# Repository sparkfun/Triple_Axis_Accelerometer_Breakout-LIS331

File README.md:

SparkFun Triple Axis Accelerometer Breakout - LIS331
========================================

[*SparkFun Triple Axis Accelerometer Breakout - LIS331 (SEN-10345)*](https://www.sparkfun.com/products/10345)

 This is a breakout board for the ultra low-power LIS331HH three axis linear accelerometer. 
 The device has a digital I2C/SPI serial interface which makes it ideal for using in embedded applications. 
 All major pins are broken out to 0.1" spaced headers. It also includes two mounting holes as well.
 
Repository Contents
-------------------

* **/Firmware** - Example code 
* **/Hardware** - Eagle design files (.brd, .sch)
* **/Production** - Production panel files (.brd)

Documentation
--------------
* **[SparkFun Fritzing repo](https://github.com/sparkfun/Fritzing_Parts)** - Fritzing diagrams for SparkFun products.
* **[SparkFun 3D Model repo](https://github.com/sparkfun/3D_Models)** - 3D models of SparkFun products. 
* **[Project Tutorial](https://learn.sparkfun.com/tutorials/raspberry-pi-zero-helmet-impact-force-monitor)** - Project tutorial using the LIS331 on a Raspberry Pi. The code used in the project uses Python and linked in a [different GitHub repository](https://github.com/jenfoxbot/ImpactForceMonitor). 

License Information
-------------------
This product is _**open source**_! 

The **hardware** is released under [Creative Commons ShareAlike 4.0 International](https://creativecommons.org/licenses/by-sa/4.0/).

The **code** is beerware; if you see me (or any other SparkFun employee) at the local, and you've found our code helpful, please buy us a round!

Please use, reuse, and modify these files as you see fit. Please maintain attribution to SparkFun Electronics and release anything derivative under the same license.

Distributed as-is; no warranty is given.

- Your friends at SparkFun.

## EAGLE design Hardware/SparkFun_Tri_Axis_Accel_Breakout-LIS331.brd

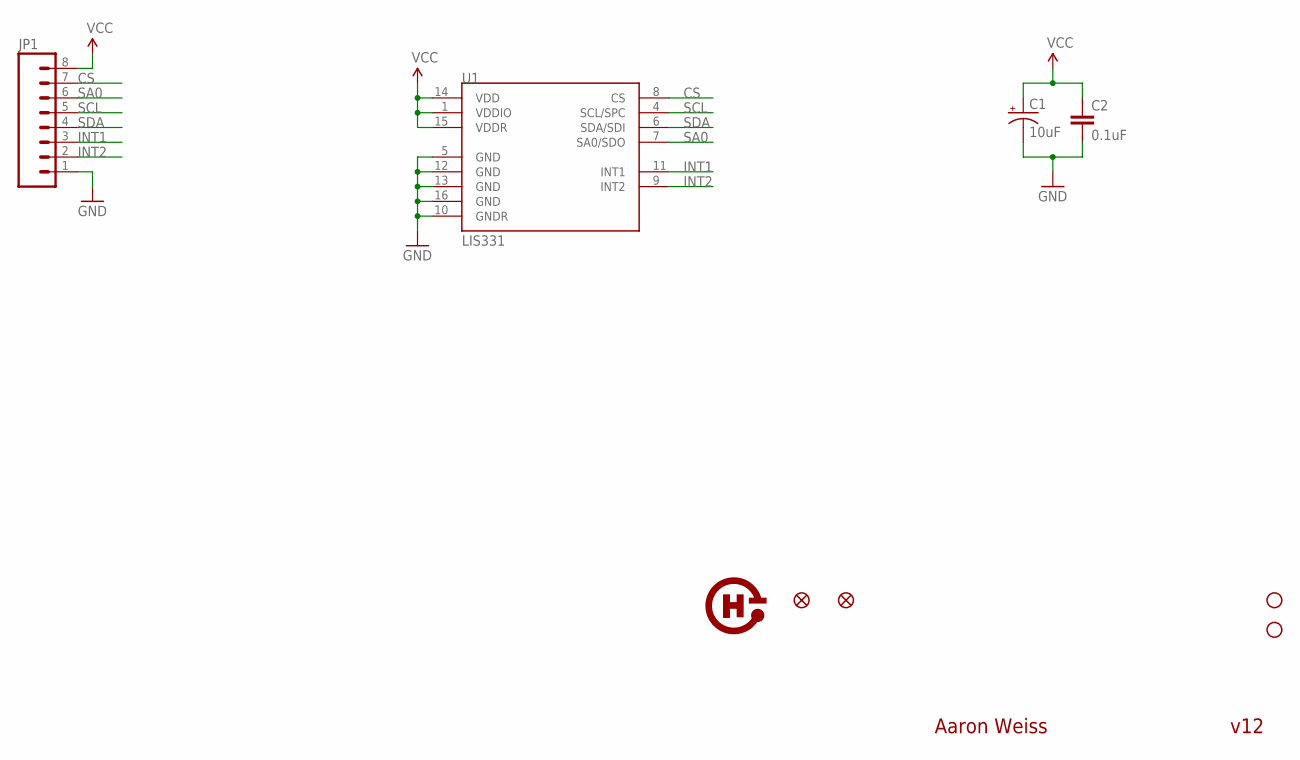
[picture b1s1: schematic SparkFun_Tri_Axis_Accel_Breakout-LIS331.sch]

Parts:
C1: 10uF; EIA3216
C2: 0.1uF; 0402-CAP
JP1: M08; 1X08
JP3, JP4: STAND-OFF
JP5, JP6: FIDUCIAL1X2; FIDUCIAL-1X2
U1: LIS331; LGA16-3MM
U$1: OSHW-LOGO-SMALL

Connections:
CS: JP1.7, U1.8 (CS)
GND: C1.C (-), C2.2, JP1.1, U1.5 (GND), U1.10 (GNDR), U1.12 (GND), U1.13 (GND), U1.16 (GND)
INT1: JP1.3, U1.11 (INT1)
INT2: JP1.2, U1.9 (INT2)
SA0: JP1.6, U1.7 (SA0/SDO)
SCL: JP1.5, U1.4 (SCL/SPC)
SDA: JP1.4, U1.6 (SDA/SDI)
VCC: C1.A (+), C2.1, JP1.8, U1.1 (VDDIO), U1.14 (VDD), U1.15 (VDDR)

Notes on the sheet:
v12
Aaron Weiss

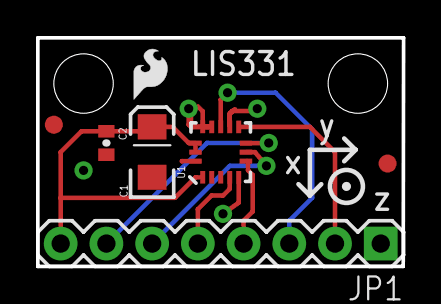
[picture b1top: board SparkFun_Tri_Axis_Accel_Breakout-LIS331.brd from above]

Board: 2 copper layers, 20.3 x 12.7 mm, 10 parts (1 on the bottom side), 8 nets.

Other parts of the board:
JP2: LOGO-SFESK; SFE-LOGO-FLAME

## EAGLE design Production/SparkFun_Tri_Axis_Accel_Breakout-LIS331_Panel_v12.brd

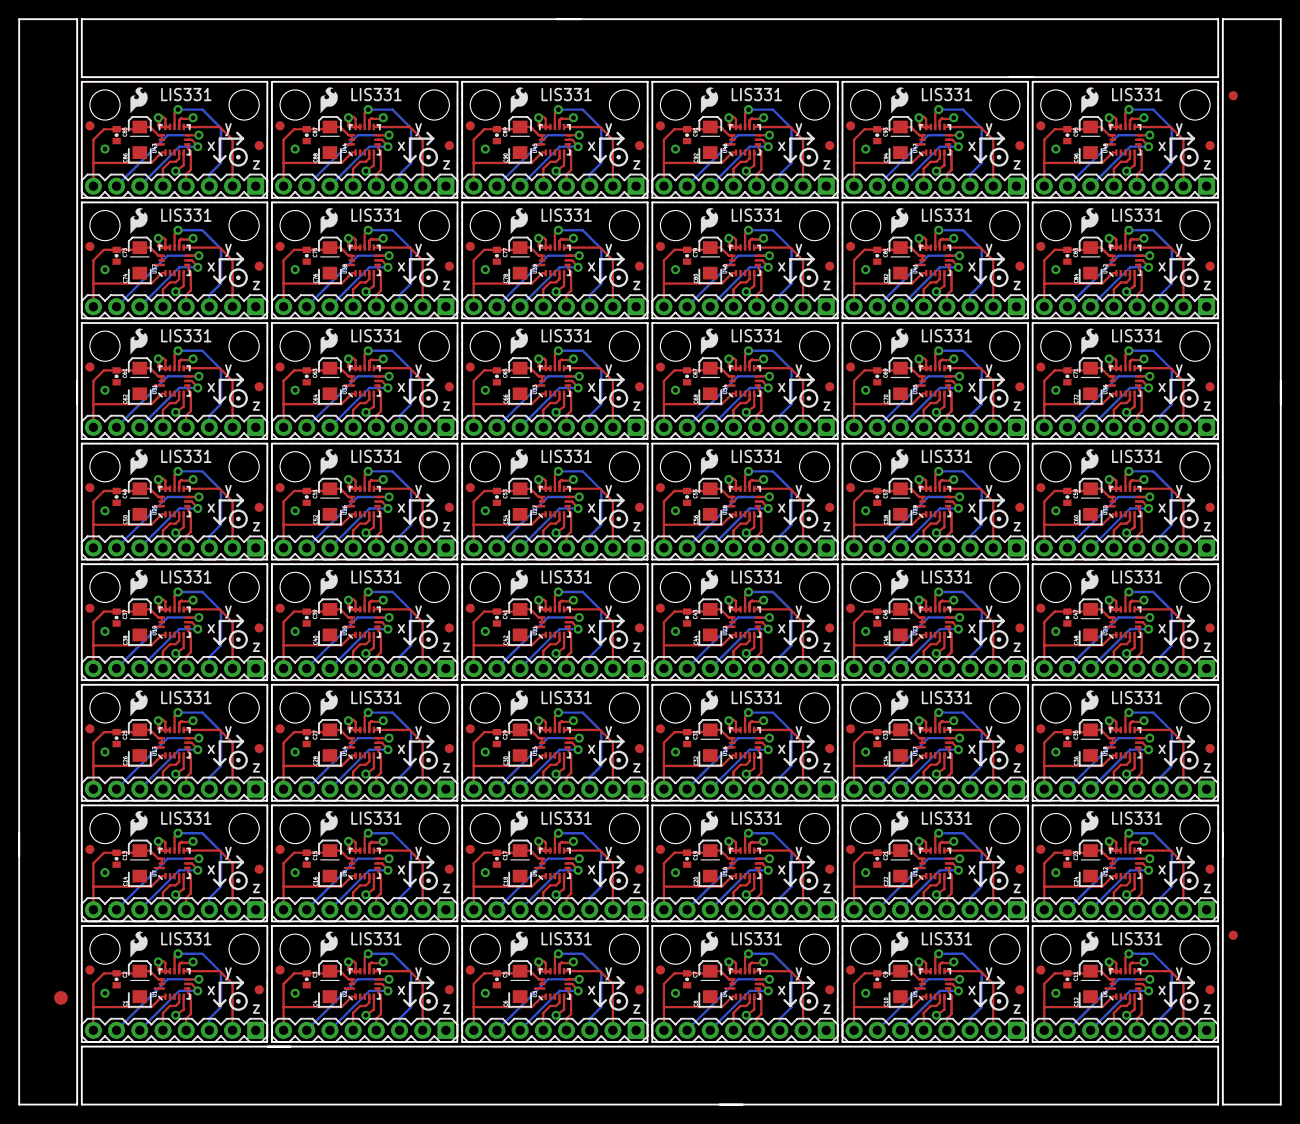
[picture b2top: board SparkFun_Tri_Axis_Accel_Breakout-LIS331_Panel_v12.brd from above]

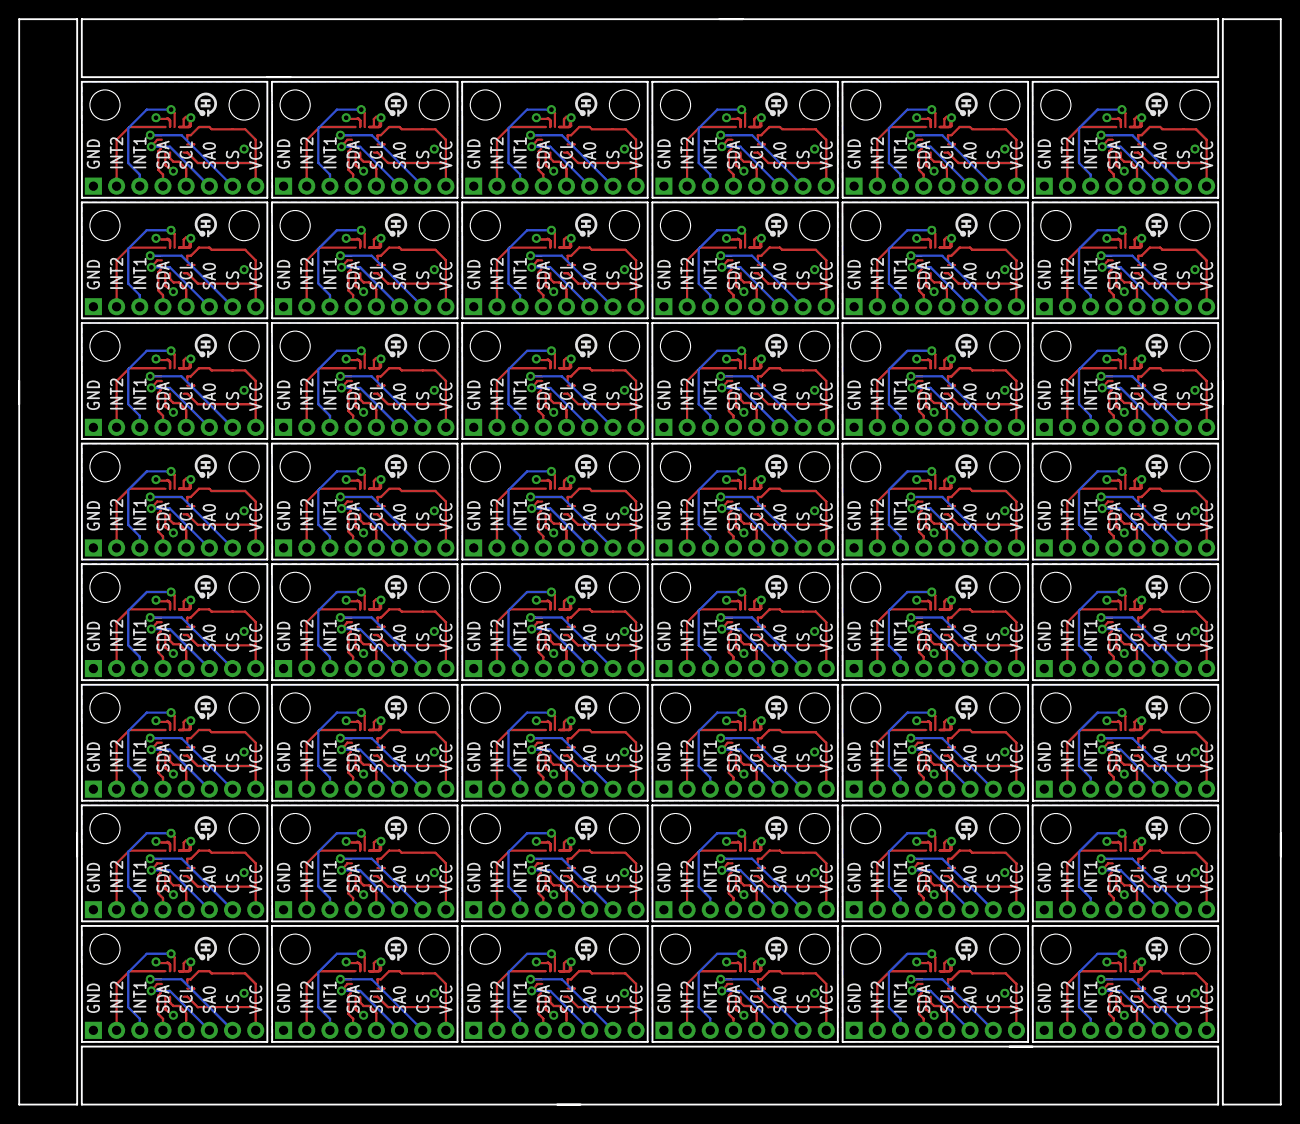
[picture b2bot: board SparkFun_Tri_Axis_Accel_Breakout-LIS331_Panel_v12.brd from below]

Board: 2 copper layers, 138.2 x 118.9 mm, 483 parts (48 on the bottom side), 384 nets.

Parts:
C1, C4, C6, C8, C10, C12, C14, C16, C18, C20, C22, C24, C26, C28, C30, C32, C34, C36, C38, C40, C42, C44, C46, C48, C50, C52, C54, C56, C58, C60, C62, C64, C66, C68, C70, C72, C74, C76, C78, C80, C82, C84, C86, C88, C90, C92, C94, C96: 10uF; EIA3216
C2, C3, C5, C7, C9, C11, C13, C15, C17, C19, C21, C23, C25, C27, C29, C31, C33, C35, C37, C39, C41, C43, C45, C47, C49, C51, C53, C55, C57, C59, C61, C63, C65, C67, C69, C71, C73, C75, C77, C79, C81, C83, C85, C87, C89, C91, C93, C95: 0.1uF; 0402-CAP
E$1: FIDUCIAL-1.5X3
E$5, E$6: FIDUCIAL-1X2
JP1, JP8, JP14, JP20, JP26, JP32, JP38, JP44, JP50, JP56, JP62, JP68, JP74, JP80, JP86, JP92, JP98, JP104, JP110, JP116, JP122, JP128, JP134, JP140, JP146, JP152, JP158, JP164, JP170, JP176, JP182, JP188, JP194, JP200, JP206, JP212, JP218, JP224, JP230, JP236, JP242, JP248, JP254, JP260, JP266, JP272, JP278, JP284: 1X08
JP2, JP7, JP13, JP19, JP25, JP31, JP37, JP43, JP49, JP55, JP61, JP67, JP73, JP79, JP85, JP91, JP97, JP103, JP109, JP115, JP121, JP127, JP133, JP139, JP145, JP151, JP157, JP163, JP169, JP175, JP181, JP187, JP193, JP199, JP205, JP211, JP217, JP223, JP229, JP235, JP241, JP247, JP253, JP259, JP265, JP271, JP277, JP283: LOGO-SFESK; SFE-LOGO-FLAME
JP3, JP4, JP9, JP10, JP15, JP16, JP21, JP22, JP27, JP28, JP33, JP34, JP39, JP40, JP45, JP46, JP51, JP52, JP57, JP58, JP63, JP64, JP69, JP70, JP75, JP76, JP81, JP82, JP87, JP88, JP93, JP94, JP99, JP100, JP105, JP106, JP111, JP112, JP117, JP118, JP123, JP124, JP129, JP130, JP135, JP136, JP141, JP142, JP147, JP148, JP153, JP154, JP159, JP160, JP165, JP166, JP171, JP172, JP177, JP178, JP183, JP184, JP189, JP190, JP195, JP196, JP201, JP202, JP207, JP208, JP213, JP214, JP219, JP220, JP225, JP226, JP231, JP232, JP237, JP238, JP243, JP244, JP249, JP250, JP255, JP256, JP261, JP262, JP267, JP268, JP273, JP274, JP279, JP280, JP285, JP286: STAND-OFF
JP5, JP6, JP11, JP12, JP17, JP18, JP23, JP24, JP29, JP30, JP35, JP36, JP41, JP42, JP47, JP48, JP53, JP54, JP59, JP60, JP65, JP66, JP71, JP72, JP77, JP78, JP83, JP84, JP89, JP90, JP95, JP96, JP101, JP102, JP107, JP108, JP113, JP114, JP119, JP120, JP125, JP126, JP131, JP132, JP137, JP138, JP143, JP144, JP149, JP150, JP155, JP156, JP161, JP162, JP167, JP168, JP173, JP174, JP179, JP180, JP185, JP186, JP191, JP192, JP197, JP198, JP203, JP204, JP209, JP210, JP215, JP216, JP221, JP222, JP227, JP228, JP233, JP234, JP239, JP240, JP245, JP246, JP251, JP252, JP257, JP258, JP263, JP264, JP269, JP270, JP275, JP276, JP281, JP282, JP287, JP288: FIDUCIAL1X2; FIDUCIAL-1X2
U1, U2, U3, U4, U5, U6, U7, U8, U9, U10, U11, U12, U13, U14, U15, U16, U17, U18, U19, U20, U21, U22, U23, U24, U25, U26, U27, U28, U29, U30, U31, U32, U33, U34, U35, U36, U37, U38, U39, U40, U41, U42, U43, U44, U45, U46, U47, U48: LIS331; LGA16-3MM
U$1, U$2, U$3, U$4, U$5, U$6, U$7, U$8, U$9, U$10, U$11, U$12, U$13, U$14, U$15, U$16, U$17, U$18, U$19, U$20, U$21, U$22, U$23, U$24, U$25, U$26, U$27, U$28, U$29, U$30, U$31, U$32, U$33, U$34, U$35, U$36, U$37, U$38, U$39, U$40, U$41, U$42, U$43, U$44, U$45, U$46, U$47, U$48: OSHW-LOGO-SMALL

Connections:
CS: JP1.7, U1.8
CS1: JP8.7, U2.8
CS2: JP14.7, U3.8
CS3: JP20.7, U4.8
CS4: JP26.7, U5.8
CS5: JP32.7, U6.8
CS6: JP38.7, U7.8
CS7: JP44.7, U8.8
CS8: JP50.7, U9.8
CS9: JP56.7, U10.8
CS10: JP62.7, U11.8
CS11: JP68.7, U12.8
CS12: JP74.7, U13.8
CS13: JP80.7, U14.8
CS14: JP86.7, U15.8
CS15: JP92.7, U16.8
CS16: JP98.7, U17.8
CS17: JP104.7, U18.8
CS18: JP110.7, U19.8
CS19: JP116.7, U20.8
CS20: JP122.7, U21.8
CS21: JP128.7, U22.8
CS22: JP134.7, U23.8
CS23: JP140.7, U24.8
CS24: JP146.7, U25.8
CS25: JP152.7, U26.8
CS26: JP158.7, U27.8
CS27: JP164.7, U28.8
CS28: JP170.7, U29.8
CS29: JP176.7, U30.8
CS30: JP182.7, U31.8
CS31: JP188.7, U32.8
CS32: JP194.7, U33.8
CS33: JP200.7, U34.8
CS34: JP206.7, U35.8
CS35: JP212.7, U36.8
CS36: JP218.7, U37.8
CS37: JP224.7, U38.8
CS38: JP230.7, U39.8
CS39: JP236.7, U40.8
CS40: JP242.7, U41.8
CS41: JP248.7, U42.8
CS42: JP254.7, U43.8
CS43: JP260.7, U44.8
CS44: JP266.7, U45.8
CS45: JP272.7, U46.8
CS46: JP278.7, U47.8
CS47: JP284.7, U48.8
GND: C1.C, C2.2, JP1.1, U1.5, U1.10, U1.12, U1.13, U1.16
GND1: C3.2, C4.C, JP8.1, U2.5, U2.10, U2.12, U2.13, U2.16
GND2: C5.2, C6.C, JP14.1, U3.5, U3.10, U3.12, U3.13, U3.16
GND3: C7.2, C8.C, JP20.1, U4.5, U4.10, U4.12, U4.13, U4.16
GND4: C9.2, C10.C, JP26.1, U5.5, U5.10, U5.12, U5.13, U5.16
GND5: C11.2, C12.C, JP32.1, U6.5, U6.10, U6.12, U6.13, U6.16
GND6: C13.2, C14.C, JP38.1, U7.5, U7.10, U7.12, U7.13, U7.16
GND7: C15.2, C16.C, JP44.1, U8.5, U8.10, U8.12, U8.13, U8.16
GND8: C17.2, C18.C, JP50.1, U9.5, U9.10, U9.12, U9.13, U9.16
GND9: C19.2, C20.C, JP56.1, U10.5, U10.10, U10.12, U10.13, U10.16
GND10: C21.2, C22.C, JP62.1, U11.5, U11.10, U11.12, U11.13, U11.16
GND11: C23.2, C24.C, JP68.1, U12.5, U12.10, U12.12, U12.13, U12.16
GND12: C25.2, C26.C, JP74.1, U13.5, U13.10, U13.12, U13.13, U13.16
GND13: C27.2, C28.C, JP80.1, U14.5, U14.10, U14.12, U14.13, U14.16
GND14: C29.2, C30.C, JP86.1, U15.5, U15.10, U15.12, U15.13, U15.16
GND15: C31.2, C32.C, JP92.1, U16.5, U16.10, U16.12, U16.13, U16.16
GND16: C33.2, C34.C, JP98.1, U17.5, U17.10, U17.12, U17.13, U17.16
GND17: C35.2, C36.C, JP104.1, U18.5, U18.10, U18.12, U18.13, U18.16
GND18: C37.2, C38.C, JP110.1, U19.5, U19.10, U19.12, U19.13, U19.16
GND19: C39.2, C40.C, JP116.1, U20.5, U20.10, U20.12, U20.13, U20.16
GND20: C41.2, C42.C, JP122.1, U21.5, U21.10, U21.12, U21.13, U21.16
GND21: C43.2, C44.C, JP128.1, U22.5, U22.10, U22.12, U22.13, U22.16
GND22: C45.2, C46.C, JP134.1, U23.5, U23.10, U23.12, U23.13, U23.16
GND23: C47.2, C48.C, JP140.1, U24.5, U24.10, U24.12, U24.13, U24.16
GND24: C49.2, C50.C, JP146.1, U25.5, U25.10, U25.12, U25.13, U25.16
GND25: C51.2, C52.C, JP152.1, U26.5, U26.10, U26.12, U26.13, U26.16
GND26: C53.2, C54.C, JP158.1, U27.5, U27.10, U27.12, U27.13, U27.16
GND27: C55.2, C56.C, JP164.1, U28.5, U28.10, U28.12, U28.13, U28.16
GND28: C57.2, C58.C, JP170.1, U29.5, U29.10, U29.12, U29.13, U29.16
GND29: C59.2, C60.C, JP176.1, U30.5, U30.10, U30.12, U30.13, U30.16
GND30: C61.2, C62.C, JP182.1, U31.5, U31.10, U31.12, U31.13, U31.16
GND31: C63.2, C64.C, JP188.1, U32.5, U32.10, U32.12, U32.13, U32.16
GND32: C65.2, C66.C, JP194.1, U33.5, U33.10, U33.12, U33.13, U33.16
GND33: C67.2, C68.C, JP200.1, U34.5, U34.10, U34.12, U34.13, U34.16
GND34: C69.2, C70.C, JP206.1, U35.5, U35.10, U35.12, U35.13, U35.16
GND35: C71.2, C72.C, JP212.1, U36.5, U36.10, U36.12, U36.13, U36.16
GND36: C73.2, C74.C, JP218.1, U37.5, U37.10, U37.12, U37.13, U37.16
GND37: C75.2, C76.C, JP224.1, U38.5, U38.10, U38.12, U38.13, U38.16
GND38: C77.2, C78.C, JP230.1, U39.5, U39.10, U39.12, U39.13, U39.16
GND39: C79.2, C80.C, JP236.1, U40.5, U40.10, U40.12, U40.13, U40.16
GND40: C81.2, C82.C, JP242.1, U41.5, U41.10, U41.12, U41.13, U41.16
GND41: C83.2, C84.C, JP248.1, U42.5, U42.10, U42.12, U42.13, U42.16
GND42: C85.2, C86.C, JP254.1, U43.5, U43.10, U43.12, U43.13, U43.16
GND43: C87.2, C88.C, JP260.1, U44.5, U44.10, U44.12, U44.13, U44.16
GND44: C89.2, C90.C, JP266.1, U45.5, U45.10, U45.12, U45.13, U45.16
GND45: C91.2, C92.C, JP272.1, U46.5, U46.10, U46.12, U46.13, U46.16
GND46: C93.2, C94.C, JP278.1, U47.5, U47.10, U47.12, U47.13, U47.16
GND47: C95.2, C96.C, JP284.1, U48.5, U48.10, U48.12, U48.13, U48.16
INT1: JP1.3, U1.11
INT2: JP1.2, U1.9
INT3: JP8.3, U2.11
INT4: JP8.2, U2.9
INT5: JP14.3, U3.11
INT6: JP14.2, U3.9
INT7: JP20.3, U4.11
INT8: JP20.2, U4.9
INT9: JP26.3, U5.11
INT10: JP26.2, U5.9
INT11: JP32.3, U6.11
INT12: JP32.2, U6.9
INT13: JP38.3, U7.11
INT14: JP38.2, U7.9
INT15: JP44.3, U8.11
INT16: JP44.2, U8.9
INT17: JP50.3, U9.11
INT18: JP50.2, U9.9
INT19: JP56.3, U10.11
INT20: JP56.2, U10.9
INT21: JP62.3, U11.11
INT22: JP62.2, U11.9
INT23: JP68.3, U12.11
INT24: JP68.2, U12.9
INT25: JP74.3, U13.11
INT26: JP74.2, U13.9
INT27: JP80.3, U14.11
INT28: JP80.2, U14.9
INT29: JP86.3, U15.11
INT30: JP86.2, U15.9
INT31: JP92.3, U16.11
INT32: JP92.2, U16.9
INT33: JP98.3, U17.11
INT34: JP98.2, U17.9
INT35: JP104.3, U18.11
INT36: JP104.2, U18.9
INT37: JP110.3, U19.11
INT38: JP110.2, U19.9
INT39: JP116.3, U20.11
INT40: JP116.2, U20.9
INT41: JP122.3, U21.11
INT42: JP122.2, U21.9
INT43: JP128.3, U22.11
INT44: JP128.2, U22.9
INT45: JP134.3, U23.11
INT46: JP134.2, U23.9
INT47: JP140.3, U24.11
INT48: JP140.2, U24.9
INT49: JP146.3, U25.11
INT50: JP146.2, U25.9
INT51: JP152.3, U26.11
INT52: JP152.2, U26.9
INT53: JP158.3, U27.11
INT54: JP158.2, U27.9
INT55: JP164.3, U28.11
INT56: JP164.2, U28.9
INT57: JP170.3, U29.11
INT58: JP170.2, U29.9
INT59: JP176.3, U30.11
INT60: JP176.2, U30.9
INT61: JP182.3, U31.11
INT62: JP182.2, U31.9
INT63: JP188.3, U32.11
INT64: JP188.2, U32.9
INT65: JP194.3, U33.11
INT66: JP194.2, U33.9
INT67: JP200.3, U34.11
INT68: JP200.2, U34.9
INT69: JP206.3, U35.11
INT70: JP206.2, U35.9
INT71: JP212.3, U36.11
INT72: JP212.2, U36.9
INT73: JP218.3, U37.11
INT74: JP218.2, U37.9
INT75: JP224.3, U38.11
INT76: JP224.2, U38.9
INT77: JP230.3, U39.11
INT78: JP230.2, U39.9
INT79: JP236.3, U40.11
INT80: JP236.2, U40.9
INT81: JP242.3, U41.11
INT82: JP242.2, U41.9
INT83: JP248.3, U42.11
INT84: JP248.2, U42.9
INT85: JP254.3, U43.11
INT86: JP254.2, U43.9
INT87: JP260.3, U44.11
INT88: JP260.2, U44.9
INT89: JP266.3, U45.11
INT90: JP266.2, U45.9
INT91: JP272.3, U46.11
INT92: JP272.2, U46.9
INT93: JP278.3, U47.11
INT94: JP278.2, U47.9
INT95: JP284.3, U48.11
INT96: JP284.2, U48.9
SA0: JP1.6, U1.7
SA1: JP8.6, U2.7
SA2: JP14.6, U3.7
SA3: JP20.6, U4.7
SA4: JP26.6, U5.7
SA5: JP32.6, U6.7
SA6: JP38.6, U7.7
SA7: JP44.6, U8.7
SA8: JP50.6, U9.7
SA9: JP56.6, U10.7
SA10: JP62.6, U11.7
SA11: JP68.6, U12.7
SA12: JP74.6, U13.7
SA13: JP80.6, U14.7
SA14: JP86.6, U15.7
SA15: JP92.6, U16.7
SA16: JP98.6, U17.7
SA17: JP104.6, U18.7
SA18: JP110.6, U19.7
SA19: JP116.6, U20.7
SA20: JP122.6, U21.7
SA21: JP128.6, U22.7
SA22: JP134.6, U23.7
SA23: JP140.6, U24.7
SA24: JP146.6, U25.7
SA25: JP152.6, U26.7
SA26: JP158.6, U27.7
SA27: JP164.6, U28.7
SA28: JP170.6, U29.7
SA29: JP176.6, U30.7
SA30: JP182.6, U31.7
SA31: JP188.6, U32.7
SA32: JP194.6, U33.7
SA33: JP200.6, U34.7
SA34: JP206.6, U35.7
SA35: JP212.6, U36.7
SA36: JP218.6, U37.7
SA37: JP224.6, U38.7
SA38: JP230.6, U39.7
SA39: JP236.6, U40.7
SA40: JP242.6, U41.7
SA41: JP248.6, U42.7
SA42: JP254.6, U43.7
SA43: JP260.6, U44.7
SA44: JP266.6, U45.7
SA45: JP272.6, U46.7
SA46: JP278.6, U47.7
SA47: JP284.6, U48.7
SCL: JP1.5, U1.4
SCL1: JP8.5, U2.4
SCL2: JP14.5, U3.4
SCL3: JP20.5, U4.4
SCL4: JP26.5, U5.4
SCL5: JP32.5, U6.4
SCL6: JP38.5, U7.4
SCL7: JP44.5, U8.4
SCL8: JP50.5, U9.4
SCL9: JP56.5, U10.4
SCL10: JP62.5, U11.4
SCL11: JP68.5, U12.4
SCL12: JP74.5, U13.4
SCL13: JP80.5, U14.4
SCL14: JP86.5, U15.4
SCL15: JP92.5, U16.4
SCL16: JP98.5, U17.4
SCL17: JP104.5, U18.4
SCL18: JP110.5, U19.4
SCL19: JP116.5, U20.4
SCL20: JP122.5, U21.4
SCL21: JP128.5, U22.4
SCL22: JP134.5, U23.4
SCL23: JP140.5, U24.4
SCL24: JP146.5, U25.4
SCL25: JP152.5, U26.4
SCL26: JP158.5, U27.4
SCL27: JP164.5, U28.4
SCL28: JP170.5, U29.4
SCL29: JP176.5, U30.4
SCL30: JP182.5, U31.4
SCL31: JP188.5, U32.4
SCL32: JP194.5, U33.4
SCL33: JP200.5, U34.4
SCL34: JP206.5, U35.4
SCL35: JP212.5, U36.4
SCL36: JP218.5, U37.4
SCL37: JP224.5, U38.4
SCL38: JP230.5, U39.4
SCL39: JP236.5, U40.4
SCL40: JP242.5, U41.4
SCL41: JP248.5, U42.4
SCL42: JP254.5, U43.4
SCL43: JP260.5, U44.4
SCL44: JP266.5, U45.4
SCL45: JP272.5, U46.4
SCL46: JP278.5, U47.4
SCL47: JP284.5, U48.4
SDA: JP1.4, U1.6
SDA1: JP8.4, U2.6
SDA2: JP14.4, U3.6
SDA3: JP20.4, U4.6
SDA4: JP26.4, U5.6
SDA5: JP32.4, U6.6
SDA6: JP38.4, U7.6
SDA7: JP44.4, U8.6
SDA8: JP50.4, U9.6
SDA9: JP56.4, U10.6
SDA10: JP62.4, U11.6
SDA11: JP68.4, U12.6
SDA12: JP74.4, U13.6
SDA13: JP80.4, U14.6
SDA14: JP86.4, U15.6
SDA15: JP92.4, U16.6
SDA16: JP98.4, U17.6
SDA17: JP104.4, U18.6
SDA18: JP110.4, U19.6
SDA19: JP116.4, U20.6
SDA20: JP122.4, U21.6
SDA21: JP128.4, U22.6
SDA22: JP134.4, U23.6
SDA23: JP140.4, U24.6
SDA24: JP146.4, U25.6
SDA25: JP152.4, U26.6
SDA26: JP158.4, U27.6
SDA27: JP164.4, U28.6
SDA28: JP170.4, U29.6
SDA29: JP176.4, U30.6
SDA30: JP182.4, U31.6
SDA31: JP188.4, U32.6
SDA32: JP194.4, U33.6
SDA33: JP200.4, U34.6
SDA34: JP206.4, U35.6
SDA35: JP212.4, U36.6
SDA36: JP218.4, U37.6
SDA37: JP224.4, U38.6
SDA38: JP230.4, U39.6
SDA39: JP236.4, U40.6
SDA40: JP242.4, U41.6
SDA41: JP248.4, U42.6
SDA42: JP254.4, U43.6
SDA43: JP260.4, U44.6
SDA44: JP266.4, U45.6
SDA45: JP272.4, U46.6
SDA46: JP278.4, U47.6
SDA47: JP284.4, U48.6
VCC: C1.A, C2.1, JP1.8, U1.1, U1.14, U1.15
VCC1: C3.1, C4.A, JP8.8, U2.1, U2.14, U2.15
VCC2: C5.1, C6.A, JP14.8, U3.1, U3.14, U3.15
VCC3: C7.1, C8.A, JP20.8, U4.1, U4.14, U4.15
VCC4: C9.1, C10.A, JP26.8, U5.1, U5.14, U5.15
VCC5: C11.1, C12.A, JP32.8, U6.1, U6.14, U6.15
VCC6: C13.1, C14.A, JP38.8, U7.1, U7.14, U7.15
VCC7: C15.1, C16.A, JP44.8, U8.1, U8.14, U8.15
VCC8: C17.1, C18.A, JP50.8, U9.1, U9.14, U9.15
VCC9: C19.1, C20.A, JP56.8, U10.1, U10.14, U10.15
VCC10: C21.1, C22.A, JP62.8, U11.1, U11.14, U11.15
VCC11: C23.1, C24.A, JP68.8, U12.1, U12.14, U12.15
VCC12: C25.1, C26.A, JP74.8, U13.1, U13.14, U13.15
VCC13: C27.1, C28.A, JP80.8, U14.1, U14.14, U14.15
VCC14: C29.1, C30.A, JP86.8, U15.1, U15.14, U15.15
VCC15: C31.1, C32.A, JP92.8, U16.1, U16.14, U16.15
VCC16: C33.1, C34.A, JP98.8, U17.1, U17.14, U17.15
VCC17: C35.1, C36.A, JP104.8, U18.1, U18.14, U18.15
VCC18: C37.1, C38.A, JP110.8, U19.1, U19.14, U19.15
VCC19: C39.1, C40.A, JP116.8, U20.1, U20.14, U20.15
VCC20: C41.1, C42.A, JP122.8, U21.1, U21.14, U21.15
VCC21: C43.1, C44.A, JP128.8, U22.1, U22.14, U22.15
VCC22: C45.1, C46.A, JP134.8, U23.1, U23.14, U23.15
VCC23: C47.1, C48.A, JP140.8, U24.1, U24.14, U24.15
VCC24: C49.1, C50.A, JP146.8, U25.1, U25.14, U25.15
VCC25: C51.1, C52.A, JP152.8, U26.1, U26.14, U26.15
VCC26: C53.1, C54.A, JP158.8, U27.1, U27.14, U27.15
VCC27: C55.1, C56.A, JP164.8, U28.1, U28.14, U28.15
VCC28: C57.1, C58.A, JP170.8, U29.1, U29.14, U29.15
VCC29: C59.1, C60.A, JP176.8, U30.1, U30.14, U30.15
VCC30: C61.1, C62.A, JP182.8, U31.1, U31.14, U31.15
VCC31: C63.1, C64.A, JP188.8, U32.1, U32.14, U32.15
VCC32: C65.1, C66.A, JP194.8, U33.1, U33.14, U33.15
VCC33: C67.1, C68.A, JP200.8, U34.1, U34.14, U34.15
VCC34: C69.1, C70.A, JP206.8, U35.1, U35.14, U35.15
VCC35: C71.1, C72.A, JP212.8, U36.1, U36.14, U36.15
VCC36: C73.1, C74.A, JP218.8, U37.1, U37.14, U37.15
VCC37: C75.1, C76.A, JP224.8, U38.1, U38.14, U38.15
VCC38: C77.1, C78.A, JP230.8, U39.1, U39.14, U39.15
VCC39: C79.1, C80.A, JP236.8, U40.1, U40.14, U40.15
VCC40: C81.1, C82.A, JP242.8, U41.1, U41.14, U41.15
VCC41: C83.1, C84.A, JP248.8, U42.1, U42.14, U42.15
VCC42: C85.1, C86.A, JP254.8, U43.1, U43.14, U43.15
VCC43: C87.1, C88.A, JP260.8, U44.1, U44.14, U44.15
VCC44: C89.1, C90.A, JP266.8, U45.1, U45.14, U45.15
VCC45: C91.1, C92.A, JP272.8, U46.1, U46.14, U46.15
VCC46: C93.1, C94.A, JP278.8, U47.1, U47.14, U47.15
VCC47: C95.1, C96.A, JP284.8, U48.1, U48.14, U48.15

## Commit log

2015-05-07 Adding hardware files, example code
2015-10-20 created new v12 panel

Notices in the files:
parts and their libraries:
SparkFun-Aesthetics: Licensing: CC v3.0 Share-Alike You are welcome to use this library for commercial purposes.
SparkFun-Retired: Licensing:Creative Commons ShareAlike 4.0 International - https://creativecommons.org/licenses/by-sa/4.0
